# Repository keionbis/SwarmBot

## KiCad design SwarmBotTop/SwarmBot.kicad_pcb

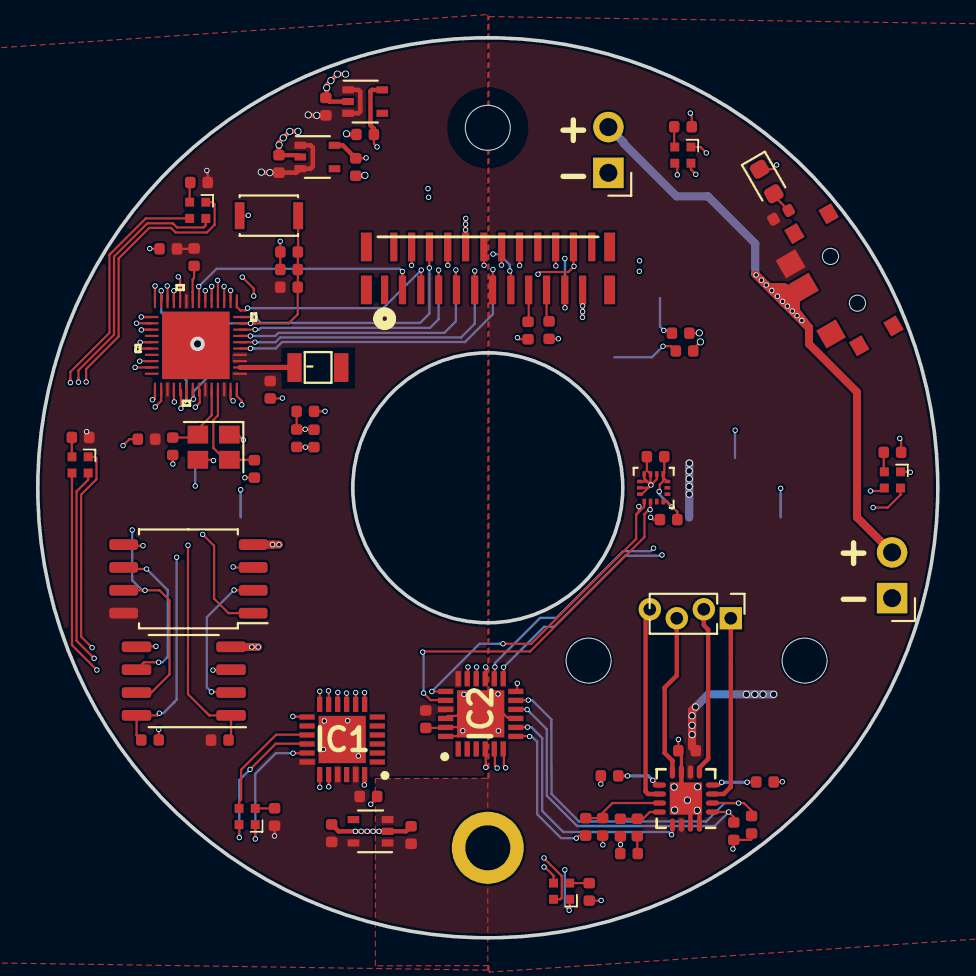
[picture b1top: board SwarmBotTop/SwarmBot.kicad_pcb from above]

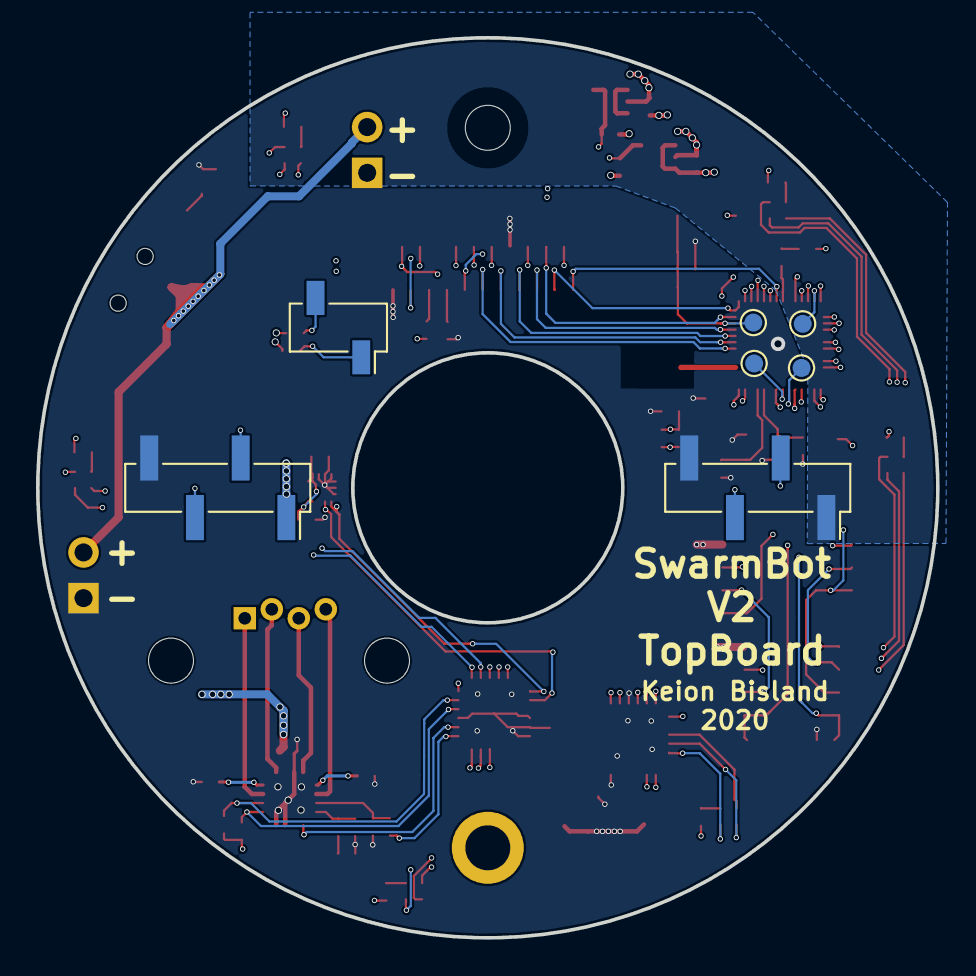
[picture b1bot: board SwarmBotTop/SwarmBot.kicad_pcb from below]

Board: 4 copper layers, 50.0 x 50.0 mm, 81 parts (7 on the bottom side), 84 nets.

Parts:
ANT1: 2450AT18B100E; ANT_2450AT18B100E
C1, C6, C14, C15, C17, C18, C19, C20, C21, C23: 1uF; C_0402_1005Metric
C2, C3, C4, C10, C12, C13, C16, C22: 0.1uF; C_0402_1005Metric
C5: 3.3nF; C_0402_1005Metric
C7: 12Pf; C_0402_1005Metric
C8: 12pF; C_0402_1005Metric
C9: 10nF; C_0402_1005Metric
C11: 22nF; C_0402_1005Metric
D1, D2, D3, D6, D7, D8: LED_ARGB; LED_SK6812_EC15_1.5x1.5mm
D4: LED; LED_0603_1608Metric
H1, H2, H10: MountingHole; MountingHole_2.5mm
H3: MountingHole_Pad; MountingHole_2.5mm_Pad
IC1, IC2: MAX7313ATG+; QFN50P400X400X80-25N
J1, J2: Conn_01x04_Female; PinHeader_1x04_P2.54mm_Vertical_SMD_Pin1Right
J3: Conn_01x04_Female; PinHeader_1x04_P1.27mm_Vertical
J5, J6: Conn_01x02_Male; PinHeader_1x02_P2.54mm_Horizontal
J7: Conn_01x02_Female; PinSocket_1x02_P2.54mm_Vertical_SMD_Pin1Right
R1, R2, R3, R5, R9, R11, R13, R20, R21, R22: 10K; R_0402_1005Metric
R4, R7, R10, R17, R18, R19: 330R; R_0402_1005Metric
R6: 20K; R_0402_1005Metric
R8, R14: 1K; R_0402_1005Metric
R12: 10k; R_0402_1005Metric
R15, R16: 200m; R_0402_1005Metric
SW1: SW_Push_Open; SW_SPST_CK_KXT3
TP1, TP2, TP3, TP4: TestPoint; TestPoint_Pad_D1.0mm
U1: ESP32-D0WD
U3: STSPIN220; QFN-16-1EP_3x3mm_P0.5mm_EP1.8x1.8mm
U4: LIS2DH; LGA-14_2x2mm_P0.35mm_LayoutBorder3x4y
U5: MIC5366-3.3YC5; SOT-353_SC-70-5
U6: MIC5366-2.8YC5; SOT-353_SC-70-5
U7: MIC5366-1.3YC5; SOT-353_SC-70-5
U8: MAX314CSE; K3-1296S-E1
U9: 62674-241121ALF; FCI_62674-241121ALF
U10: ESP-PSRAM64; SOP-8_3.9x4.9mm_P1.27mm
U11: XM25QH32B; SOIC-8_5.275x5.275mm_P1.27mm
Y1: 40MHz; Crystal_SMD_2520-4Pin_2.5x2.0mm

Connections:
+1V35: C20.1, U7.5, U9.15
+2V8: C19.1, U6.5, U9.21
+3V3: C1.1, C2.2, C3.2, C4.2, C6.1, C12.1, C13.1, C15.1, C18.1, C21.1, IC1.18, IC1.21, IC1.23, IC2.18, IC2.21, R2.1, R3.2, R4.2, R5.1, R7.2, R10.2, R11.1, R13.1, R17.2, R18.2, R19.2, R20.1, R21.1, R22.1, U1.1, U1.3, U1.4, U1.19, U1.37, U1.43, U1.46, U4.4, U4.7, U4.8, U5.5, U6.1, U6.3, U7.1, U7.3, U9.14, U11.8
+4V: J5.2, J6.2, U8.1
+BATT: C14.1, C17.2, J1.1, J2.1, R9.2, U3.6, U3.14, U5.1, U5.3, U8.2
/Sheet5DAF9EB0/A1_3: J3.1, U3.3
/Sheet5DAF9EB0/A2_3: J3.2, U3.5
/Sheet5DAF9EB0/B1_3: J3.3, U3.8
/Sheet5DAF9EB0/B2_3: J3.4, U3.10
/Sheet5DAF9EB0/CAPTOUCH: H3.1, U1.12
/Sheet5DAF9EB0/CMD: U1.30, U10.7, U11.7
/Sheet5DAF9EB0/CURRSET: IC2.7, R8.2
/Sheet5DAF9EB0/Camera/PDWN: R1.2, U9.17
/Sheet5DAF9EB0/Camera/RESET: R2.2, U9.19
/Sheet5DAF9EB0/EN: C16.1, C23.2, R5.2, SW1.2, TP4.1, U1.9
/Sheet5DAF9EB0/IO0: TP3.1, U1.23
/Sheet5DAF9EB0/IO4: U1.24, U9.12
/Sheet5DAF9EB0/IO13: U1.20, U9.4
/Sheet5DAF9EB0/IO14: U1.17, U9.3
/Sheet5DAF9EB0/IO16: U1.25, U11.1
/Sheet5DAF9EB0/IO17: U1.27, U10.2, U11.2
/Sheet5DAF9EB0/IO25: U1.14, U9.8
/Sheet5DAF9EB0/IO27: U1.16, U9.16
/Sheet5DAF9EB0/IO34: U1.10, U9.6
/Sheet5DAF9EB0/IO35: U1.11, U9.5
/Sheet5DAF9EB0/IO37: U1.6, U9.11
/Sheet5DAF9EB0/IO38: U1.7, U9.9
/Sheet5DAF9EB0/LEDS/L0: D1.2, IC2.4
/Sheet5DAF9EB0/LEDS/L1: D1.3, IC2.5
/Sheet5DAF9EB0/LEDS/L2: D1.4, IC2.6
/Sheet5DAF9EB0/LEDS/L3: D2.4, IC2.15
/Sheet5DAF9EB0/LEDS/L4: D2.3, IC2.16
/Sheet5DAF9EB0/LEDS/L5: D2.2, IC2.17
/Sheet5DAF9EB0/LEDS/L6: D3.4, IC2.12
/Sheet5DAF9EB0/LEDS/L7: D3.2, IC2.14
/Sheet5DAF9EB0/LEDS/L8: D3.3, IC2.13
/Sheet5DAF9EB0/LEDS/L9: D6.4, IC1.11
/Sheet5DAF9EB0/LEDS/L10: D6.3, IC1.12
/Sheet5DAF9EB0/LEDS/L11: D6.2, IC1.13
/Sheet5DAF9EB0/LEDS/L12: D7.4, IC1.17
/Sheet5DAF9EB0/LEDS/L13: D7.3, IC1.16
/Sheet5DAF9EB0/LEDS/L14: D7.2, IC1.15
/Sheet5DAF9EB0/LEDS/L15: D8.4, IC1.7
/Sheet5DAF9EB0/LEDS/L16: D8.3, IC1.8
/Sheet5DAF9EB0/LEDS/L17: D8.2, IC1.10
/Sheet5DAF9EB0/LMOTDIR: J1.3, U1.22
/Sheet5DAF9EB0/LMOTSTEP: J1.2, U1.21
/Sheet5DAF9EB0/PENDIR: IC2.11, R13.2, U3.2
/Sheet5DAF9EB0/PENSTEP: IC2.10, R11.2, U3.1
/Sheet5DAF9EB0/RMOTDIR: J2.3, U1.13
/Sheet5DAF9EB0/RMOTSTEP: J2.2, U1.15
/Sheet5DAF9EB0/RX: TP1.1, U1.40
/Sheet5DAF9EB0/SCL: IC1.19, IC2.19, J7.2, R21.2, U1.39, U4.1
/Sheet5DAF9EB0/SCL1: U1.36, U9.20
/Sheet5DAF9EB0/SD0: U1.32, U10.3, U11.3
/Sheet5DAF9EB0/SD1: U1.33, U10.5, U11.5
/Sheet5DAF9EB0/SD3: R22.2, U1.29, U10.1
/Sheet5DAF9EB0/SDA: IC1.20, IC2.20, J7.1, R20.2, U1.42, U4.2
/Sheet5DAF9EB0/SDA1: U1.35, U9.22
/Sheet5DAF9EB0/SD_CLK: U10.6, U11.6
/Sheet5DAF9EB0/STEPPEREN: IC2.8, U3.13
/Sheet5DAF9EB0/S_VN: U1.8, U9.7
/Sheet5DAF9EB0/S_VP: U1.5, U9.13
/Sheet5DAF9EB0/TX: TP2.1, U1.41
GND: C1.2, C2.1, C3.1, C4.1, C6.2, C7.1, C8.1, C9.1, C10.2, C11.2, C12.2, C13.2, C14.2, C15.2, C16.2, C17.1, C18.2, C19.2, C20.2, C21.2, C22.1, C23.1, D4.1, IC1.9, IC1.24, IC1.25, IC2.9, IC2.23, IC2.24, IC2.25, J1.4, J2.4, J5.1, J6.1, R1.1, R12.2, R15.1, R16.1, SW1.1, U1.49, U3.7, U3.15, U3.16, U3.17, U4.9, U4.10, U4.11, U4.12, U4.13, U4.14, U5.2, U6.2, U7.2, U9.10, U9.23, U10.4, U11.4, Y1.1, Y1.3
unnamed: ANT1.1, U1.2
unnamed: C5.1, C9.2, R6.1, U1.48
unnamed: C5.2, R6.2, U1.47
unnamed: C7.2, U1.45, Y1.4
unnamed: C8.2, U1.44, Y1.2
unnamed: C10.1, R8.1, U3.11
unnamed: C11.1, R14.2
unnamed: D1.1, R17.1
unnamed: D2.1, R18.1
unnamed: D3.1, R19.1
unnamed: D4.2, R9.1
unnamed: D6.1, R4.1
unnamed: D7.1, R7.1
unnamed: D8.1, R10.1
unnamed: R3.1, U1.18
unnamed: R12.1, R14.1, U3.12
unnamed: R15.2, U3.4
unnamed: R16.2, U3.9
VDD_SDIO: C22.2, U1.26, U10.8

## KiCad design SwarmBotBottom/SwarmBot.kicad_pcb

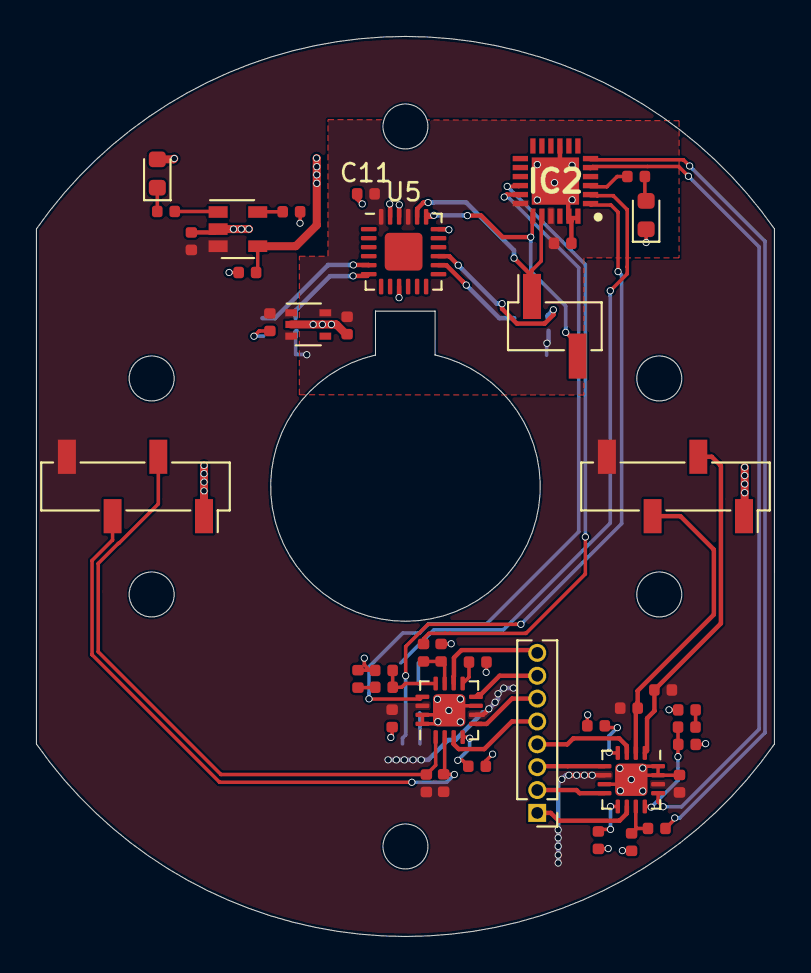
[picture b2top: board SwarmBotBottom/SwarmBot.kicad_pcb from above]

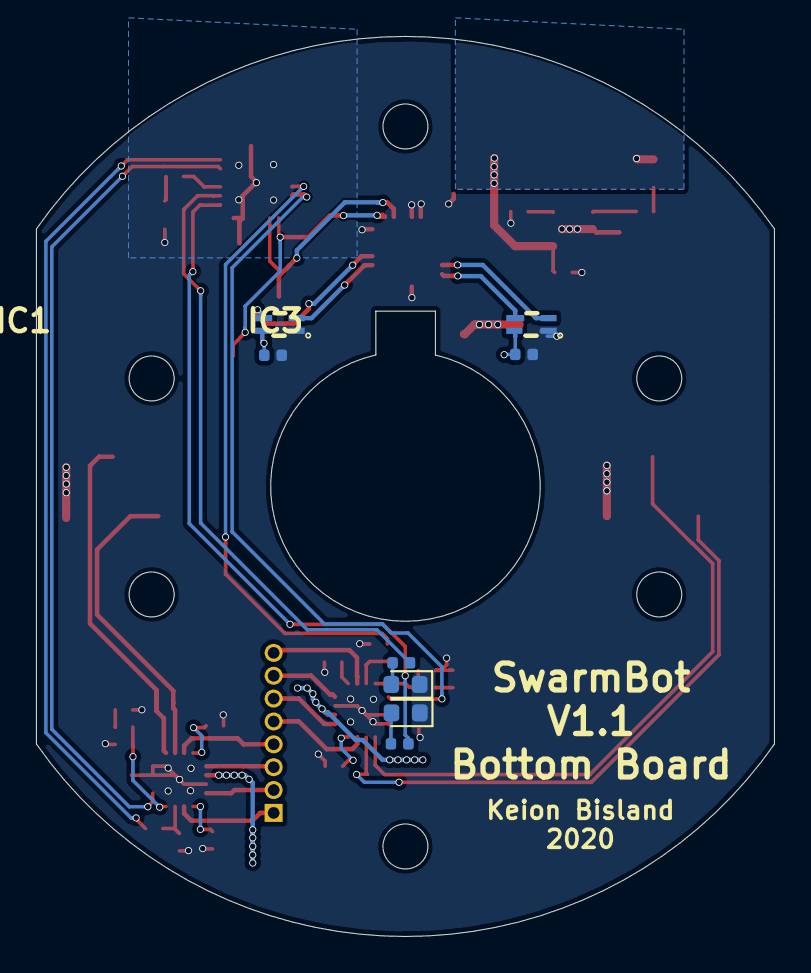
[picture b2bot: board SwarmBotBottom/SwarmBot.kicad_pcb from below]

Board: 2 copper layers, 41.0 x 50.0 mm, 55 parts (8 on the bottom side), 45 nets.

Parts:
C1, C4, C7, C10, C12: 0.1uF; C_0402_1005Metric
C2, C5: 22nF; C_0402_1005Metric
C3, C6, C8, C9, C20, C21: 1uF; C_0402_1005Metric
C11: 10uF; C_0402_1005Metric
D1, D2, D4: WHITE; LED_0603_1608Metric
D5: UV; LED_0603_1608Metric
H3, H4, H5, H6, H7, H8: MountingHole; MountingHole_2.5mm
IC1, IC3: VEML6040A3OG
IC2: MAX7313ATG+; QFN50P400X400X80-25N
J1, J2: Conn_01x04_Male; PinSocket_1x04_P2.54mm_Vertical_SMD_Pin1Right
J3: Conn_01x02_Male; PinHeader_1x02_P2.54mm_Vertical_SMD_Pin1Right
J6: Conn_01x08_Female; PinHeader_1x08_P1.27mm_Vertical
R1, R6, R9, R14: 1K; R_0402_1005Metric
R3, R5, R11, R13: 10K; R_0402_1005Metric
R4, R12: 10k; R_0402_1005Metric
R7, R8, R19, R20: 200m; R_0402_1005Metric
R15, R18: 470R; R_0402_1005Metric
R16, R17, R22: 330R; R_0402_1005Metric
U1, U2: STSPIN220; VQFN-16-1EP_3x3mm_P0.5mm_EP1.8x1.8mm
U3: MIC5366-3.3YC5; SOT-353_SC-70-5
U4: MCP73831-2-OT; SOT-23-5
U5: TCA9548AMRGER; Texas_RGE0024C_EP2.1x2.1mm

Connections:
+3V3: C7.1, C9.1, C10.2, C11.2, C12.1, IC1.4, IC2.18, IC2.21, IC3.4, U3.5, U5.21, U5.24
+5V: C20.1, D2.2, U4.4
+BATT: C3.2, C6.2, C8.1, C21.2, J1.4, J2.4, R3.1, R5.1, R11.1, R13.1, U1.6, U1.14, U2.6, U2.14, U3.1, U3.3, U4.3
/Sheet5DAF9EF1/A1: J6.4, U2.3
/Sheet5DAF9EF1/A1_2: J6.5, U1.3
/Sheet5DAF9EF1/A2: J6.3, U2.5
/Sheet5DAF9EF1/A2_2: J6.6, U1.5
/Sheet5DAF9EF1/B1: J6.1, U2.10
/Sheet5DAF9EF1/B1_2: J6.8, U1.10
/Sheet5DAF9EF1/B2: J6.2, U2.8
/Sheet5DAF9EF1/B2_2: J6.7, U1.8
/Sheet5DAF9EF1/CURRSETL: IC2.6, R9.2
/Sheet5DAF9EF1/CURRSETR: IC2.16, R1.2
/Sheet5DAF9EF1/IRLED: IC2.1, R16.2
/Sheet5DAF9EF1/M1DIR: J1.2, R11.2, U2.1
/Sheet5DAF9EF1/M1STEP: J1.3, R13.2, U2.2
/Sheet5DAF9EF1/M2DIR: J2.2, R3.2, U1.1
/Sheet5DAF9EF1/M2STEP: J2.3, R5.2, U1.2
/Sheet5DAF9EF1/POWERLED: IC2.3, R17.2
/Sheet5DAF9EF1/SCL: IC2.19, J3.2, U5.19
/Sheet5DAF9EF1/SCL1: IC1.3, U5.15
/Sheet5DAF9EF1/SCL2: IC3.3, U5.6
/Sheet5DAF9EF1/SDA: IC2.20, J3.1, U5.20
/Sheet5DAF9EF1/SDA1: IC1.2, U5.14
/Sheet5DAF9EF1/SDA2: IC3.2, U5.5
/Sheet5DAF9EF1/STEPPERENL: IC2.5, U2.13
/Sheet5DAF9EF1/STEPPERENR: IC2.17, U1.13
/Sheet5DAF9EF1/UVLED: IC2.2, R22.2
GND: C1.2, C2.2, C3.1, C4.2, C5.2, C6.1, C7.2, C8.2, C9.2, C10.1, C11.1, C12.2, C20.2, C21.1, D1.1, D4.1, D5.1, IC1.1, IC2.9, IC2.23, IC2.24, IC2.25, IC3.1, J1.1, J2.1, R4.2, R7.1, R8.1, R12.2, R15.2, R19.1, R20.1, U1.7, U1.15, U1.16, U1.17, U2.7, U2.15, U2.16, U2.17, U3.2, U4.2, U5.9, U5.18, U5.22, U5.23
unnamed: C1.1, R1.1, U1.11
unnamed: C2.1, R6.2
unnamed: C4.1, R9.1, U2.11
unnamed: C5.1, R14.2
unnamed: D1.2, R16.1
unnamed: D2.1, R18.1
unnamed: D4.2, R17.1
unnamed: D5.2, R22.1
unnamed: R4.1, R6.1, U1.12
unnamed: R7.2, U1.4
unnamed: R8.2, U1.9
unnamed: R12.1, R14.1, U2.12
unnamed: R15.1, U4.5
unnamed: R18.2, U4.1
unnamed: R19.2, U2.4
unnamed: R20.2, U2.9

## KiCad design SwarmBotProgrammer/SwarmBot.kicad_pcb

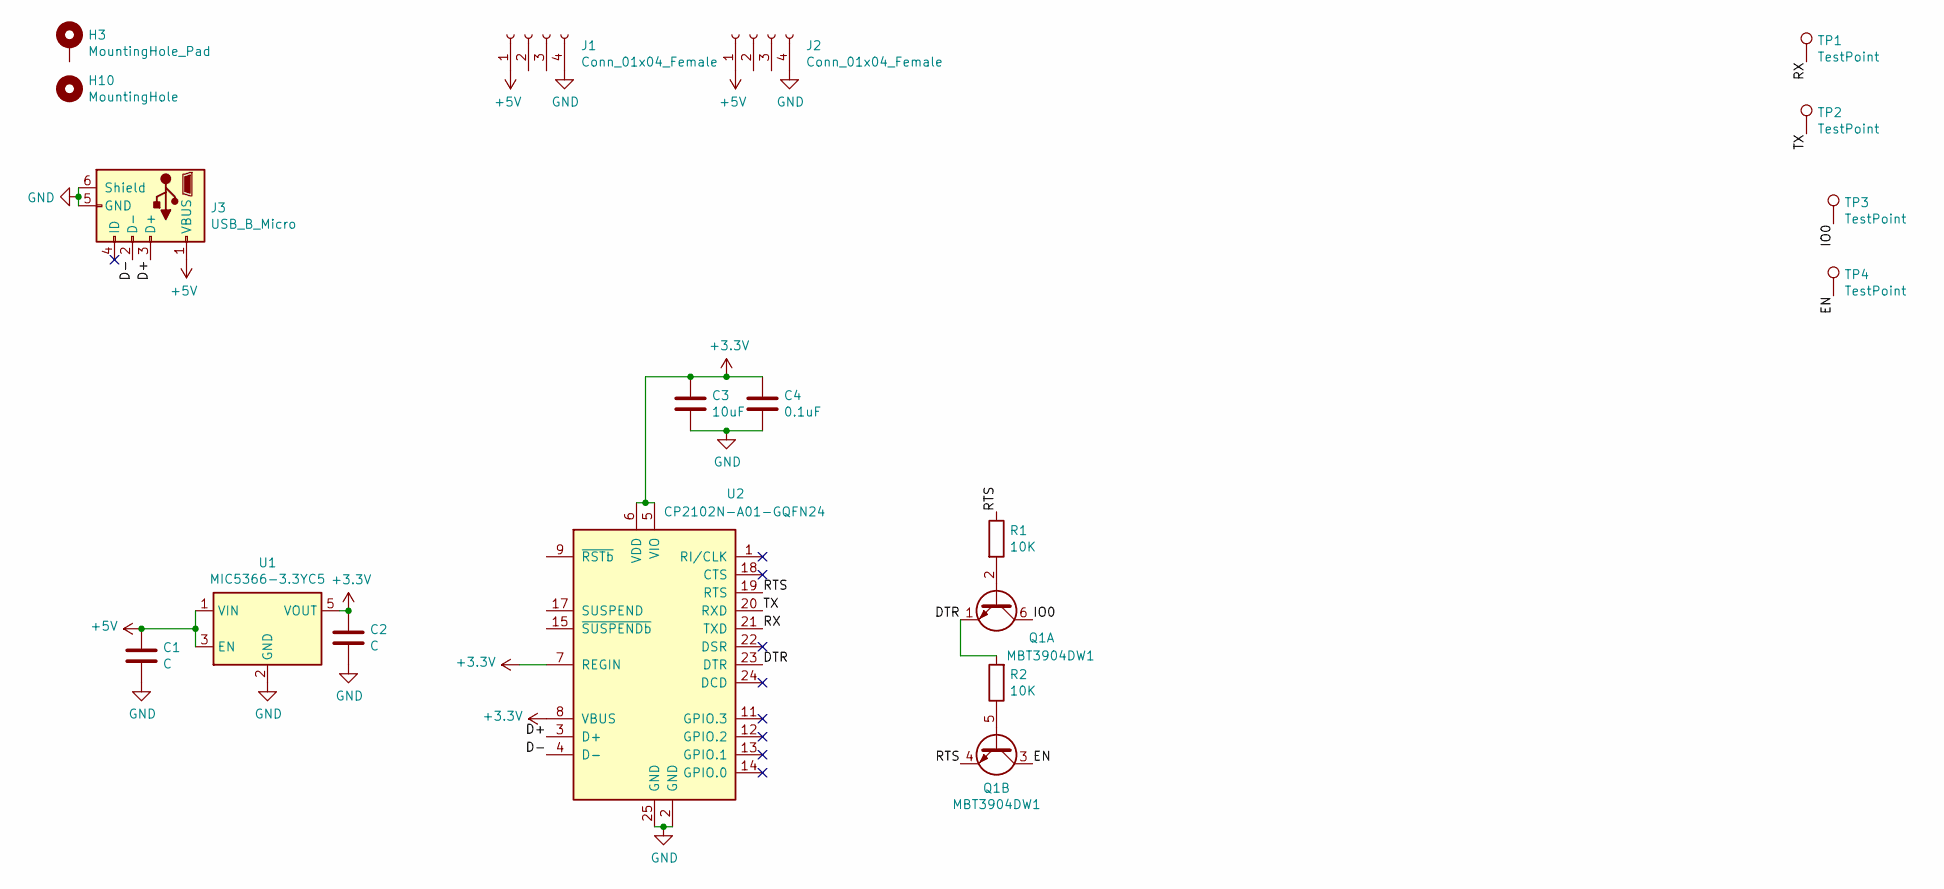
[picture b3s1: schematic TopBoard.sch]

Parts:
C1, C2: C; C_0402_1005Metric
C3: 10uF; C_0402_1005Metric
C4: 0.1uF; C_0402_1005Metric
H3: MountingHole_Pad; MountingHole_2.5mm_Pad
H10: MountingHole; MountingHole_2.5mm
J1, J2: Conn_01x04_Female; PinHeader_1x04_P2.54mm_Vertical_SMD_Pin1Right
J3: USB_B_Micro; USB_Micro-B_Molex_47346-0001
Q1: MBT3904DW1; SOT-363_SC-70-6
R1, R2: 10K; R_0402_1005Metric
TP1, TP2, TP3, TP4: TestPoint; TestPoint_Pad_D1.0mm
U1: MIC5366-3.3YC5; SOT-353_SC-70-5
U2: CP2102N-A01-GQFN24; QFN-24-1EP_4x4mm_P0.5mm_EP2.6x2.6mm

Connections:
+3V3: C2.1, C3.1, C4.1, U1.5 (VOUT), U2.5 (VIO), U2.6 (VDD), U2.7 (REGIN), U2.8 (VBUS)
+5V: C1.1, J1.1, J2.1, J3.1 (VBUS), U1.1 (VIN), U1.3 (EN)
/Sheet5DAF9EB0/D+: J3.3 (D+), U2.3 (D+)
/Sheet5DAF9EB0/D-: J3.2 (D-), U2.4 (D-)
/Sheet5DAF9EB0/DTR: Q1.1 (E1), R2.2, U2.23 (DTR)
/Sheet5DAF9EB0/EN: Q1.3 (C2), TP4.1
/Sheet5DAF9EB0/IO0: Q1.6 (C1), TP3.1
/Sheet5DAF9EB0/RTS: Q1.4 (E2), R1.1, U2.19 (RTS)
/Sheet5DAF9EB0/RX: TP1.1, U2.21 (TXD)
/Sheet5DAF9EB0/TX: TP2.1, U2.20 (RXD)
GND: C1.2, C2.2, C3.2, C4.2, J1.4, J2.4, J3.5 (GND), J3.6 (Shield), U1.2 (GND), U2.2 (GND), U2.25 (GND)
unnamed: Q1.2 (B1), R1.2
unnamed: Q1.5 (B2), R2.1

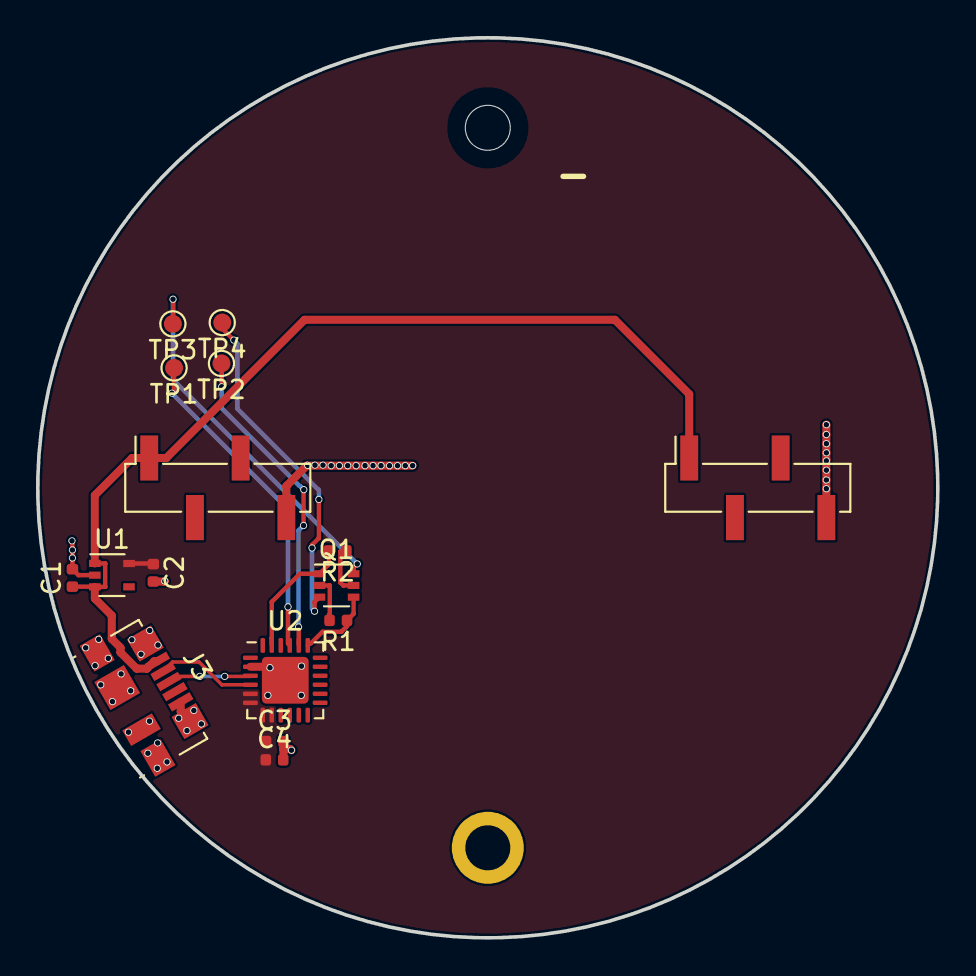
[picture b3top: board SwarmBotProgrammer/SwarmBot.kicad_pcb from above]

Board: 2 copper layers, 50.0 x 50.0 mm, 18 parts (0 on the bottom side), 13 nets.

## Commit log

2019-12-05 Both Boards
2019-12-18 Camera routing with all sensors and motors
2019-12-20 V1 ready to order
2019-12-28 things
2020-04-22 Final Design
2020-04-30 Updated LED drivers

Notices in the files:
parts and their libraries:
Copyright 2016 Accelerated Designs. All rights reserved.
